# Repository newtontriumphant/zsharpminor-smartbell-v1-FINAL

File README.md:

# zsharpminor's SmartBell, v1!

Hi, thanks for reviewing my project! ;w; This is an ESP32-powered smart doorbell with smart AI-powered detection, that automatically captures a picture that is sent to a Discord webhook via WiFi when the doorbell is rung, which triggers an integration that can set off a custom ringtone on a mobile app. Features near-waterproof PETG/TPU case and a temperature sensor that automatically reports Temperature and Humidity to said webhook as well. Additionally, an ultrasonic sensor detects movement and wakes up the camera to take a picture and identify it through a simple ML algorithm. NOTE: This is a software-heavy project, I am aiming for this to be a Tier 4 project, and Tanook agreed that it qualifies as Tier 4 (under the condition that a CAD case exists, which it does!).

I built this project for a few reasons: firstly, the doorbell I have is non-functional, and I can't be asked to give Amazon 100 dollars of my hard-earned money to sell my data through a Ring doorbell. Secondly, I wanted some more experience in building a near-100% waterproof case design with PETG and TPU gaskets. The goal of this project was to keep the total cost under half that of a commercially available substitute - and still get the thrill of designing it myself; I think that I did a good job. Screenshots of the CAD design (both assembled and unassembled) are at the bottom of the README.

BOM CSV FILE: https://docs.google.com/spreadsheets/d/1LvQgwua6umSP1ob7BG9KYe2bF_PC_YEmnamfS4FcfZg/

(BOM and placement CSV files also placed inside the PCB folder for easy access).

# BOM:

**GRANT REQUIRED: $30.00**

Screenshots of Carts:

1x SEEED Studios

1x JLCPCB

Grant:

* 1x SEEED Studios XIAO ESP32-S3 SENSE (**requires Grant**).
* 1x 2-Layer JLCPCB (**requires Grant**).

Self-Provided:

* 1x Standard Active Buzzer (Self-Provided)
* 1x 5mm Diameter Green Standard LED (Self-Provided)
* 1x 330 Ohm Resistor for LED (Self-Provided)
* 1x 12mm Tactswitch and Cover (Self-Provided)
* 4x Female Header, Right Angle (Self-Provided)
* 1x Adafruit STEMMA QT to 4-pin Male Cable (Self-Provided)
* 1x Adafruit AHT20 STEMMA I2C Temp/Humi Sensor (Self-Provided)
* 1x HC-SR04 45 x 70 mm Ultrasonic Sensor (Self-Provided)
* 1x 1500mah JST LiPo Battery (Self-Provided)

* 1x Case to be entirely 3d-printed in near-waterproof PETG with TPU seals (self-provided), iterations may occur.

(NOTE: the case intentionally has an empty space to the right; this is for the AHT20 temp/humi sensor as well as a LiPo battery (I'm experimenting with a few battery sizes!)

PCB will be glued to the back of the case, and the top will be water sealed with a TPU gasket and water-resistant sealant.

# Empty CAD case:

# Final CAD model with case, showcasing how the components fit together:

## No. 1: PCB in case without top:

## No. 2: PCB in case with top:

## No. 3: Side-View of USB-C port and tapered edges

# Schematic:

# PCB:

# PCB 3d Render:

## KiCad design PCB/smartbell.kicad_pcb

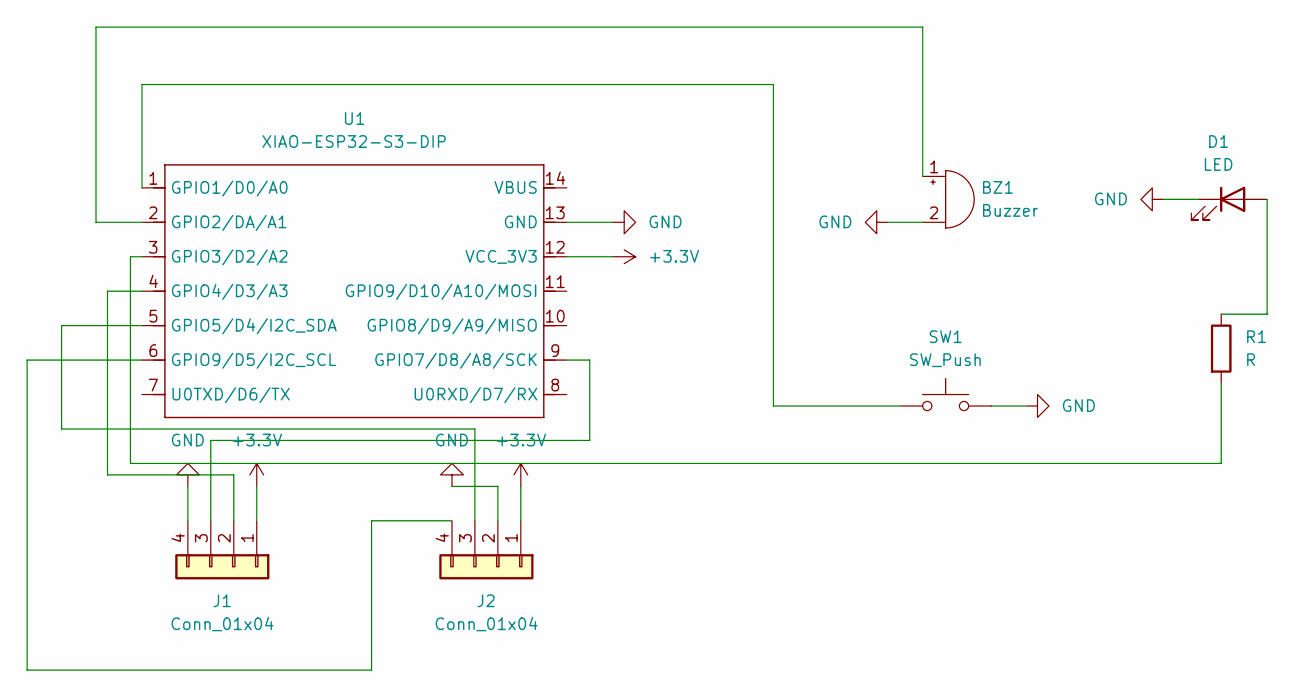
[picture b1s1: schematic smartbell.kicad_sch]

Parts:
BZ1: Buzzer; Buzzer_12x9.5RM7.6
D1: LED; LED_D5.0mm
J1, J2: Conn_01x04; PinHeader_1x04_P2.54mm_Horizontal
R1: R; R_Axial_DIN0207_L6.3mm_D2.5mm_P10.16mm_Horizontal
SW1: SW_Push; SW_PUSH-12mm
U1: XIAO-ESP32-S3-DIP; XIAO-ESP32S3-DIP

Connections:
+3.3V: J1.1, J2.1, U1.12 (VCC_3V3)
GND: BZ1.2 (-), D1.1 (K), J1.4, J2.2, SW1.2, U1.13 (GND)
unnamed: BZ1.1 (+), U1.2 (GPIO2/DA/A1)
unnamed: D1.2 (A), R1.1
unnamed: J1.2, U1.4 (GPIO4/D3/A3)
unnamed: J1.3, U1.9 (GPIO7/D8/A8/SCK)
unnamed: J2.3, U1.5 (GPIO5/D4/I2C_SDA)
unnamed: J2.4, U1.6 (GPIO9/D5/I2C_SCL)
unnamed: SW1.1, U1.1 (GPIO1/D0/A0)
unnamed: R1.2, U1.3 (GPIO3/D2/A2)

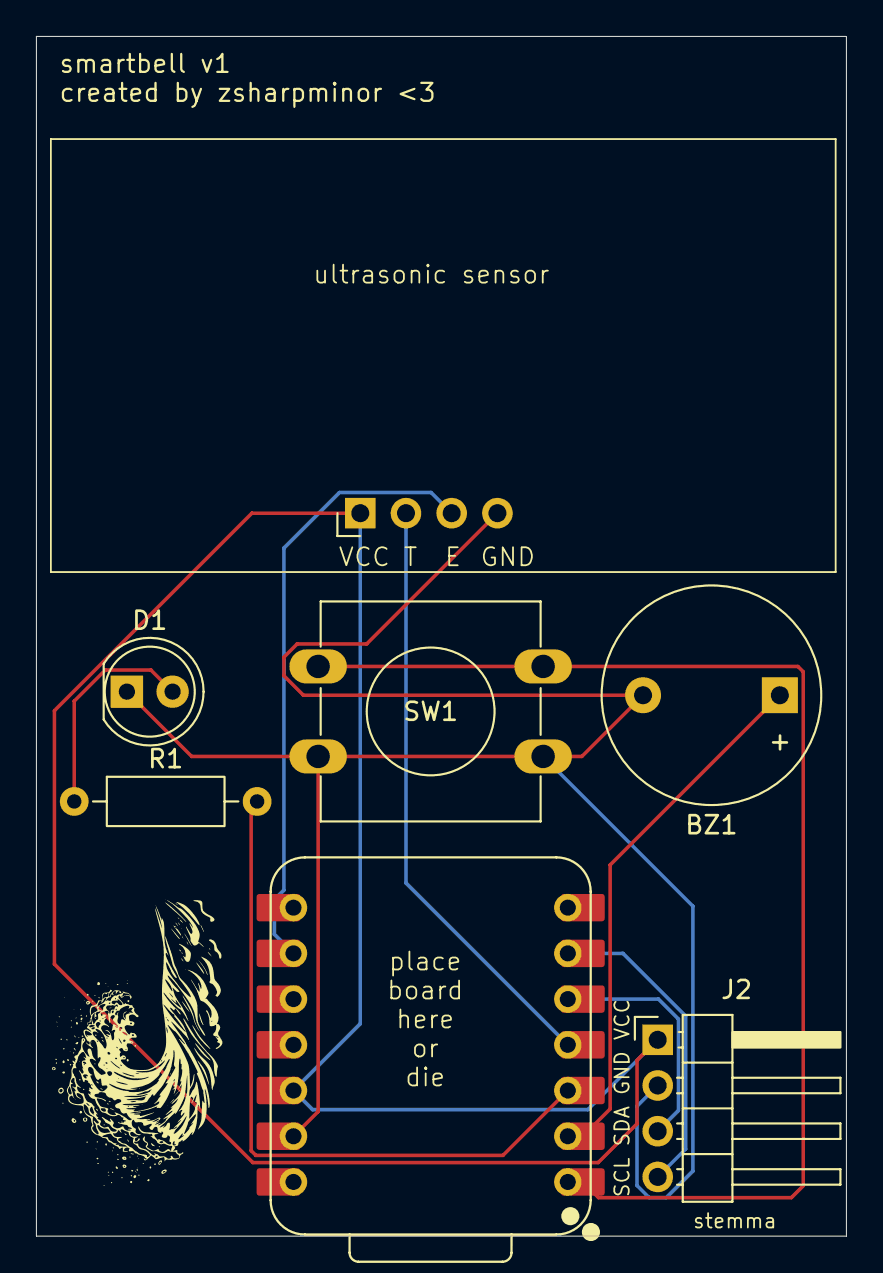
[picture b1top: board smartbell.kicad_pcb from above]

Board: 2 copper layers, 45.0 x 66.7 mm, 7 parts (0 on the bottom side), 10 nets.

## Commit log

2025-12-03 Updated README with BOM and extensive proof. Please approve ;w;
2025-12-03 added PCB directory
2025-12-03 Added ALL Final PCB files.
2025-12-03 Added ALL Final PCB Files. <3
2025-12-03 Added Final Case CAD File
2025-12-03 Update README.md with FINAL CHANGES
2025-12-03 Update README.md with Final Changes <3
2025-12-03 Added Final CAD Files <3
2025-12-03 Added All Final Firmware Files <3
2025-12-03 Final Changes <3
2025-12-03 Added 3D Model of PCB Only <3
